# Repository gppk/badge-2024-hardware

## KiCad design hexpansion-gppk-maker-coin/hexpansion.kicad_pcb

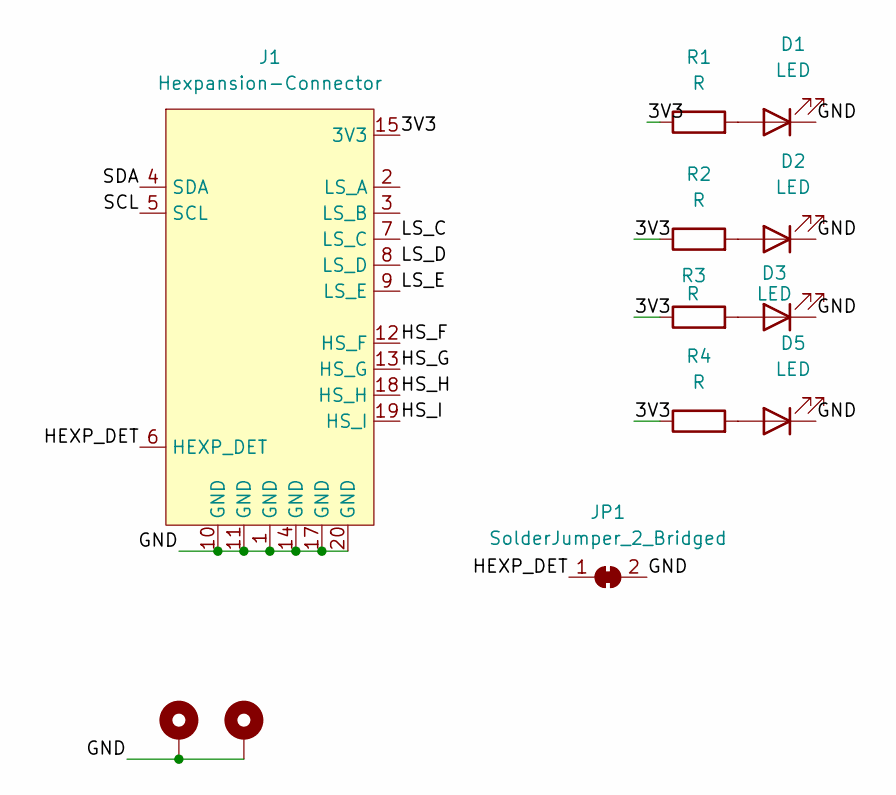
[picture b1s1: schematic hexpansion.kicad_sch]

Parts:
D1, D2, D3, D5: LED; LED_0805_2012Metric
H1, H2: MountingHole_Pad; MountingHole_2.2mm_M2_Pad_Via
J1: Hexpansion-Connector; hexpansion-edge-connector
JP1: SolderJumper_2_Bridged; SolderJumper-2_P1.3mm_Bridged_RoundedPad1.0x1.5mm
R1, R2, R3, R4: R; R_0603_1608Metric

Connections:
/3V3: J1.15 (3V3), J1.16 (3V3), R1.1, R2.1, R3.1, R4.1
/GND: D1.1 (K), D2.1 (K), D3.1 (K), D5.1 (K), H1.1, H2.1, J1.1 (GND), J1.10 (GND), J1.11 (GND), J1.14 (GND), J1.17 (GND), J1.20 (GND), JP1.2 (B); also elsewhere on the board
/HEXP_DET: J1.6 (HEXP_DET), JP1.1 (A)
/HS_F: J1.12 (HS_F)
/HS_G: J1.13 (HS_G)
/HS_H: J1.18 (HS_H)
/HS_I: J1.19 (HS_I)
/LS_C: J1.7 (LS_C)
/LS_D: J1.8 (LS_D)
/LS_E: J1.9 (LS_E)
/SCL: J1.5 (SCL)
/SDA: J1.4 (SDA)
unnamed: D1.2 (A), R1.2
unnamed: D2.2 (A), R2.2
unnamed: D3.2 (A), R3.2
unnamed 15: D5.2 (A), R4.2; also elsewhere on the board

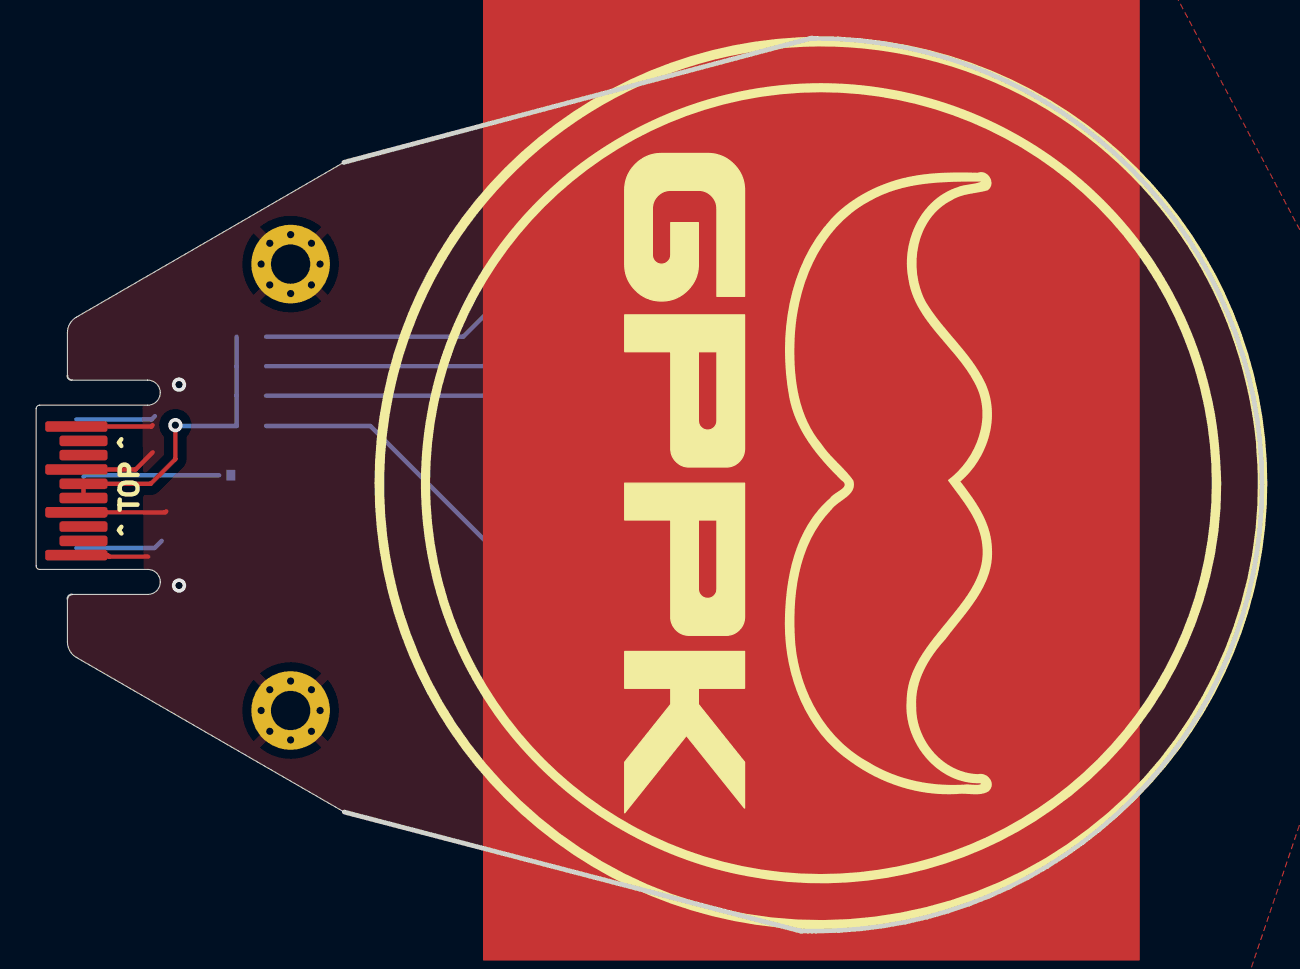
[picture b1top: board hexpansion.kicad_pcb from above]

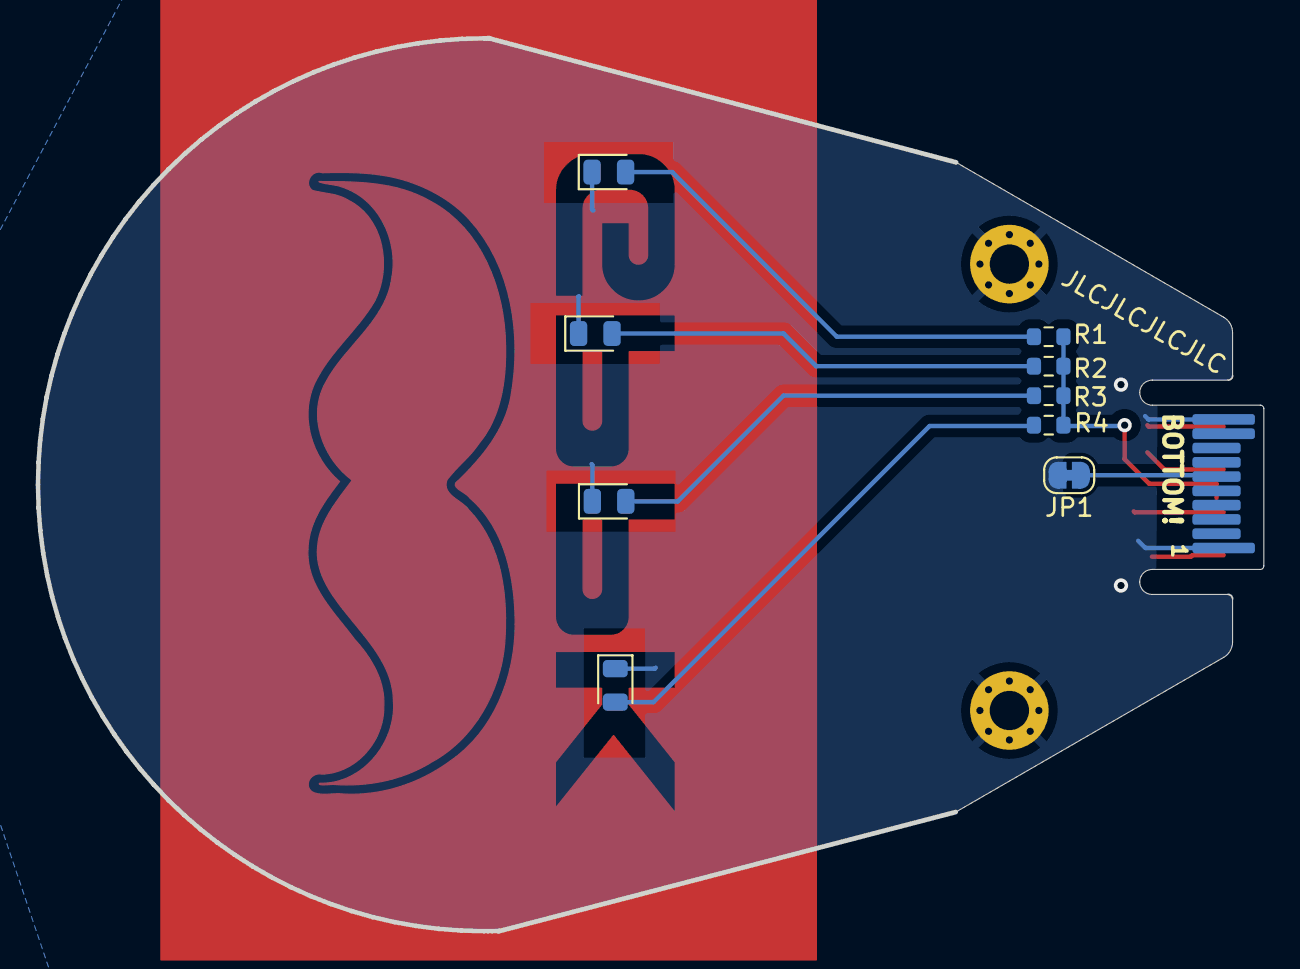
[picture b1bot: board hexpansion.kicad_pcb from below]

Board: 2 copper layers, 68.7 x 50.0 mm, 12 parts (9 on the bottom side), 7 nets.

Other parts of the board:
D4: LED; LED_0805_2012Metric

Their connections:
/GND: D4.1 (K); also elsewhere on the board
unnamed 15: D4.2 (A); also elsewhere on the board

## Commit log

2024-04-06 baseline copy
2024-04-06 Inkscape project file with used output files
2024-04-06 Kicad Project Files
2024-04-06 For first review
2024-04-08 Final PCB fab
